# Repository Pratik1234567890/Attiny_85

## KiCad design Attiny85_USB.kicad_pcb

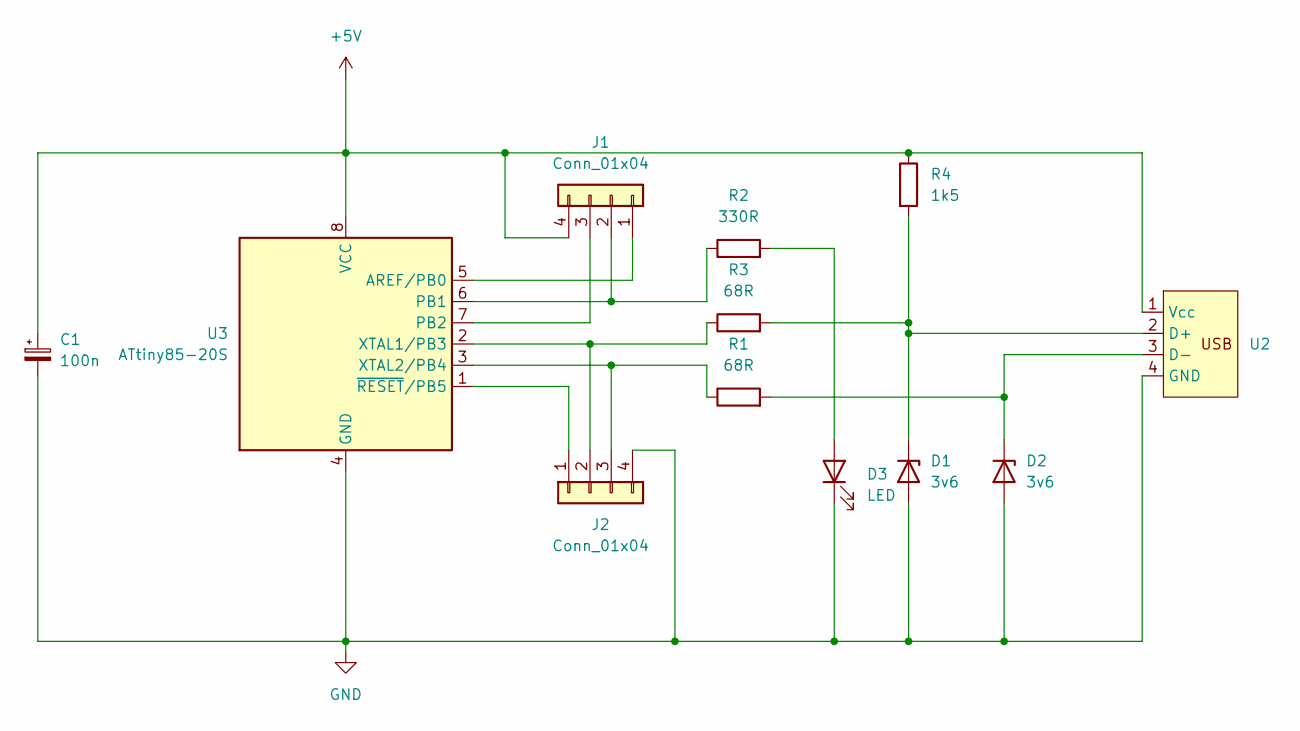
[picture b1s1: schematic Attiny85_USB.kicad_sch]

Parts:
C1: 100n; C_1206_3216Metric_Pad1.33x1.80mm_HandSolder
D1, D2: 3v6; D_SOD-123
D3: LED; LED_D3.0mm
J1, J2: Conn_01x04; FanPinHeader_1x04_P2.54mm_Vertical
R1, R3: 68R; R_0805_2012Metric_Pad1.20x1.40mm_HandSolder
R2: 330R; R_0805_2012Metric_Pad1.20x1.40mm_HandSolder
R4: 1k5; R_0805_2012Metric_Pad1.20x1.40mm_HandSolder
U2: PCB_USB_Connector
U3: ATtiny85-20S; SOIC-8W_5.3x5.3mm_P1.27mm

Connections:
+5V: C1.1, J1.4, R4.1, U2.1 (Vcc), U3.8 (VCC)
GND: C1.2, D1.2 (A), D2.2 (A), D3.1 (K), J2.4, U2.4 (GND), U3.4 (GND)
unnamed: D1.1 (K), R3.2, R4.2, U2.2 (D+)
unnamed: D2.1 (K), R1.2, U2.3 (D-)
unnamed: D3.2 (A), R2.2
unnamed: J1.1, U3.5 (AREF/PB0)
unnamed: J1.2, R2.1, U3.6 (PB1)
unnamed: J1.3, U3.7 (PB2)
unnamed: J2.1, U3.1 (~RESET/PB5)
unnamed: J2.2, R3.1, U3.2 (XTAL1/PB3)
unnamed: J2.3, R1.1, U3.3 (XTAL2/PB4)

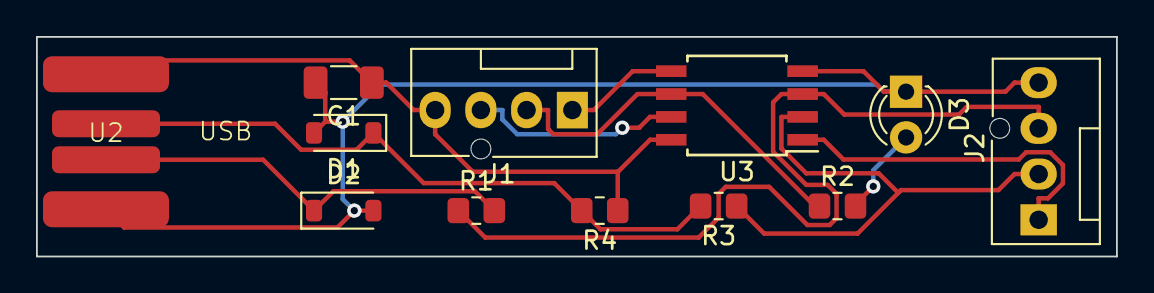
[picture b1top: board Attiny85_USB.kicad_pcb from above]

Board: 2 copper layers, 60.0 x 12.2 mm, 12 parts (0 on the bottom side), 11 nets.

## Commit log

2023-12-26 uploaded upon the completion of thr project
